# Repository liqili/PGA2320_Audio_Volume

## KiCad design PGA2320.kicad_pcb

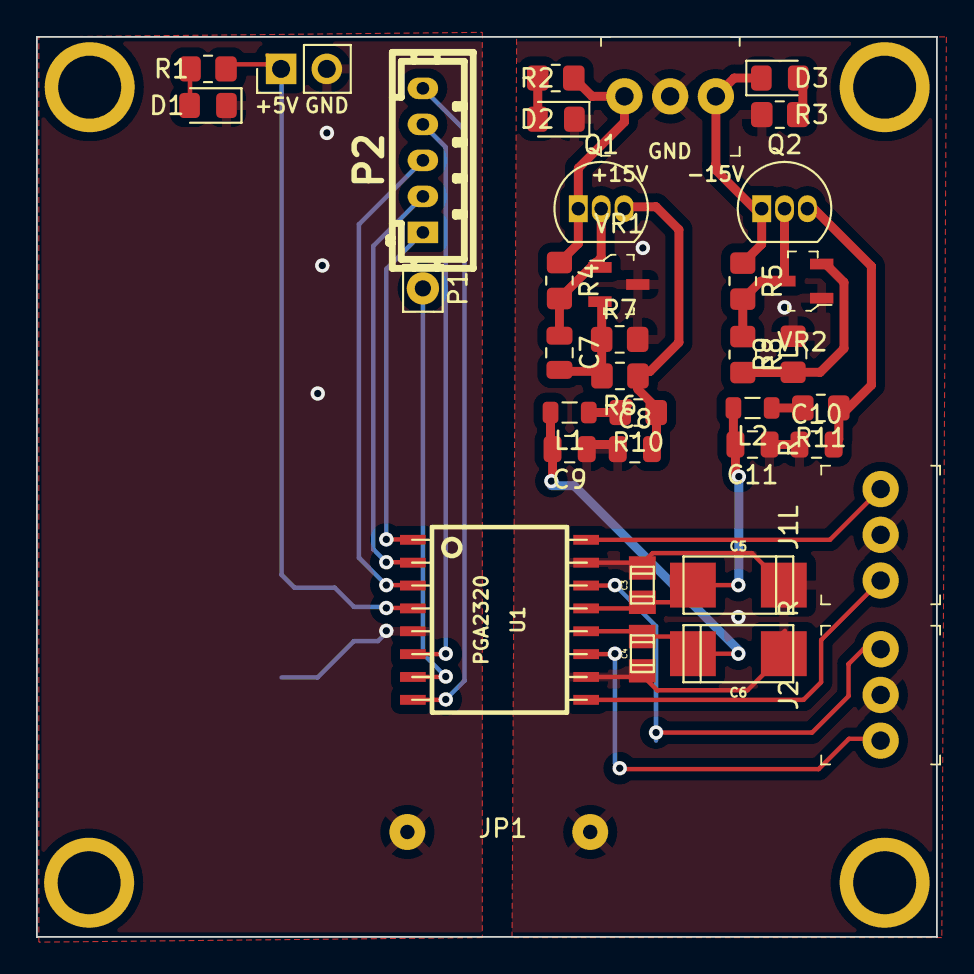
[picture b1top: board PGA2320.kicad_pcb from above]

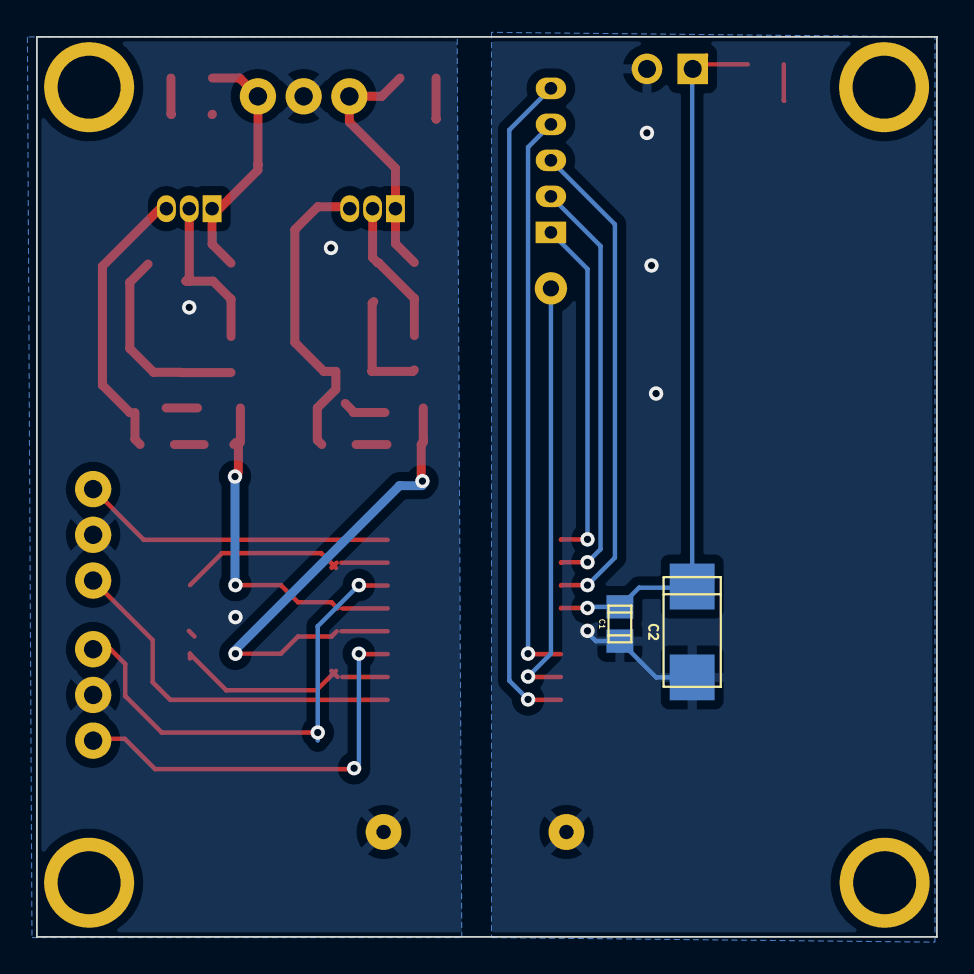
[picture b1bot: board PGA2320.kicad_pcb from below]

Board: 2 copper layers, 50.0 x 50.0 mm, 39 parts (2 on the bottom side), 28 nets.

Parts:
C1: 0.1uf; c_0805
C2: 10uf; c_tant_C
C3, C4: 0.1uF; c_0805
C5, C6: 10uF; c_tant_C
C7: 100pf; C_0805_2012Metric
C8, C9, C10, C11: 10uf; C_0805_2012Metric
D1, D2, D3: LED; LED_0805_2012Metric_Pad1.15x1.40mm_HandSolder
J1, J2: XH2.54-3P; PinHeader_1x3_P2.54mm_Drill1.02mm
J3: 2P-2.54; PinHeader_1x02_P2.54mm_Vertical
J4: 3P-2.54; PinHeader_1x3_P2.54mm_Drill1.02mm
JP1: JUMPER; WireConnection_0-8mmDrill
L1, L2: 47uH; L_0805_2012Metric
P1: SDO_TO_OTHER_PGA2311; Pin_D0.9mm_L10.0mm_W2.4mm_FlatFork
P2: CONTROLLER; b5b-ph-kl
Q1: BC550; TO-92_Inline
Q2: BC560; TO-92_Inline
R1, R2, R3: 10k; R_0805_2012Metric_Pad1.20x1.40mm_HandSolder
R4, R5: 1k; R_0805_2012Metric_Pad1.20x1.40mm_HandSolder
R6: 25k; R_0805_2012Metric_Pad1.20x1.40mm_HandSolder
R7, R8: 5k; R_0805_2012Metric_Pad1.20x1.40mm_HandSolder
R9: 26.2k; R_0805_2012Metric_Pad1.20x1.40mm_HandSolder
R10, R11: 10; R_0805_2012Metric_Pad1.20x1.40mm_HandSolder
U1: PGA2320; soic-16-PGA2320
VR1, VR2: TL431AIDBZR; SOT-23-3

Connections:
+5VD: C1.1, C2.1, J3.1, R1.2, U1.4 (VD+)
+15V: C4.1, C6.1, C9.2, L1.2, U1.12 (VA+)
-15V: C3.2, C5.2, C11.2, L2.2, U1.13 (VA-)
/+16V to +18V: J4.1, Q1.1 (C), R2.1, R4.1
/-16V to -18V: D3.1 (K), J4.3, Q2.1 (C), R5.1
CS: P2.2, U1.2 (*CS)
GND_A: C3.1, C4.2, C5.1, C6.2, C8.1, C9.1, C10.1, C11.1, D2.1 (K), J1.2, J2.2, J4.2, JP1.1 (A), R3.1, R7.2, R9.2, U1.10 (AGNDR), U1.15 (AGNDL), VR1.3 (A), VR2.1 (K)
GND_D: C1.2, C2.2, D1.1 (K), J3.2, JP1.2 (B), U1.5 (DGND)
MUTE: P2.5, U1.8 (*MUTE)
unnamed: D1.2 (A), R1.1
unnamed: D2.2 (A), R2.2
unnamed: D3.2 (A), R3.2
unnamed: L1.1, R10.2
unnamed: L2.1, R11.2
unnamed: C7.1, Q1.2 (B), R4.2, VR1.1 (K)
unnamed: C8.2, Q1.3 (E), R6.1, R10.1
unnamed: Q2.2 (B), R5.2, R8.1, VR2.3 (A)
unnamed: C10.2, Q2.3 (E), R11.1
unnamed: C7.2, R6.2, R7.1, VR1.2 (REF)
unnamed: R8.2, R9.1, VR2.2 (REF)
SCLK: P2.4, U1.6 (SCLK)
SDI: P2.3, U1.3 (SDI)
SDO: P1.1, U1.7 (SDO)
VIN_L: J1.1, U1.16 (VINL)
VIN_R: J1.3, U1.9 (VINR)
VOUT_L: J2.1, U1.14 (VOUTL)
VOUT_R: J2.3, U1.11 (VOUTR)
ZCEN: P2.1, U1.1 (ZCEN)

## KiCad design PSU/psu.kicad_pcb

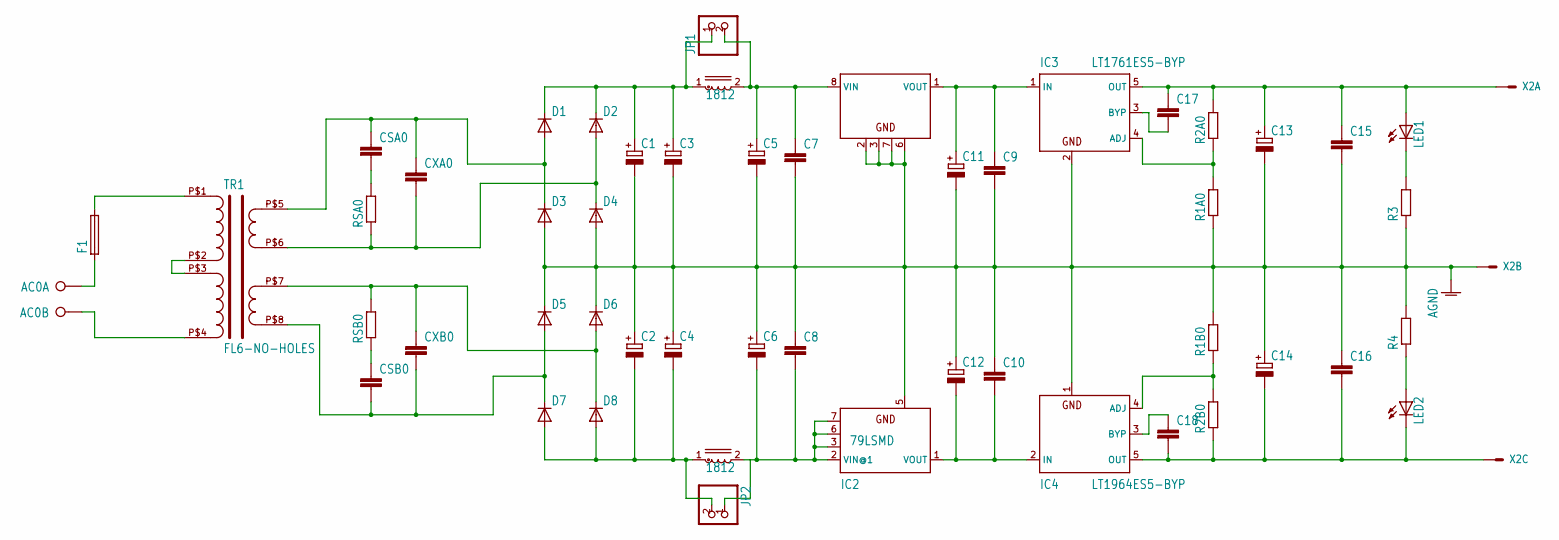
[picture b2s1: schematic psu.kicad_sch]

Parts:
AC0: W237-02P; W237-132
C1, C2, C3, C4, C5, C6: CPOL-EUE5-10.5; E5-10,5
C7, C8, C9, C10, C17, C18: C-EUC1206; C1206
C11, C12, C13, C14: CPOL-EUD; PANASONIC_D
C15, C16: C-EUC4532; C4532
CSA0: C-EUC1210; C1210
CSB0: C-EUC1210; C1210
CXA0: C-EUC1210; C1210
CXB0: C-EUC1210; C1210
D1, D2, D3, D4, D5, D6, D7, D8: DIODE-DO214AC; DO214AC
F1: GSH15
IC1: 78LSMD; SOIC08
IC2: 79LSMD; SOIC08
IC3: LT1761ES5-BYP; SOT23-5
IC4: LT1964ES5-BYP; SOT23-5
JP1, JP2: PINHD-1X2; 1X02
L1, L2: 1812
LED1, LED2: LEDCHIPLED_0805; CHIPLED_0805
R1A0, R1B0, R2A0, R2B0: R-EU_R0805; R0805
R3, R4: R-EU_R1206; R1206
RSA0: R-EU_R1206; R1206
RSB0: R-EU_R1206; R1206
TR1: FL6-NO-HOLES
X2: 22-23-2031

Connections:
AGND: C1.-, C2.+, C3.-, C4.+, C5.-, C6.+, C7.2, C8.1, C9.2, C10.1, C11.-, C12.+, C13.-, C14.+, C15.2, C16.1, D3.A, D4.A, D5.C, D6.C, IC1.2 (GND@1), IC1.3 (GND@2), IC1.6 (GND@4), IC1.7 (GND@3), IC2.5 (GND), IC3.2 (GND), IC4.1 (GND), R1A0.1, R1B0.2, R3.1, R4.2, X2.2
C14: C14.-, C16.2, C18.2, IC4.5 (OUT), LED2.C, R2B0.1, X2.3
unnamed: TR1.P$2 (PRI1B), TR1.P$3 (PRI2A)
unnamed: F1.2, TR1.P$1 (PRI1A)
unnamed: AC0.2, TR1.P$4 (PRI2B)
unnamed: AC0.1, F1.1
unnamed: CSA0.2, RSA0.2
unnamed: LED2.A, R4.1
unnamed: C17.2, IC3.3 (BYP)
unnamed: LED1.C, R3.2
unnamed: C9.1, C11.+, IC1.1 (VOUT), IC3.1 (IN)
unnamed: C13.+, C15.1, C17.1, IC3.5 (OUT), LED1.A, R2A0.2, X2.1
unnamed: IC4.4 (ADJ), R1B0.1, R2B0.2
unnamed: IC3.4 (ADJ), R1A0.2, R2A0.1
unnamed: CXA0.2, D2.A, D4.C, RSA0.1, TR1.P$6 (SEC1B)
unnamed: CSA0.1, CXA0.1, D1.A, D3.C, TR1.P$5 (SEC1A)
unnamed: CSB0.2, CXB0.2, D5.A, D7.C, TR1.P$8 (SEC2B)
unnamed: C10.2, C12.-, IC2.1 (VOUT), IC4.2 (IN)
unnamed: C18.1, IC4.3 (BYP)
unnamed: C5.+, C7.1, IC1.8 (VIN), JP1.2, L1.2
unnamed: C2.-, C4.-, D7.A, D8.A, JP2.2, L2.1
unnamed: C6.-, C8.2, IC2.2 (VIN@1), IC2.3 (VIN@2), IC2.6 (VIN@3), IC2.7 (VIN@4), JP2.1, L2.2
unnamed: CXB0.1, D6.A, D8.C, RSB0.2, TR1.P$7 (SEC2A)
unnamed: CSB0.1, RSB0.1
unnamed: C1.+, C3.+, D1.C, D2.C, JP1.1, L1.1

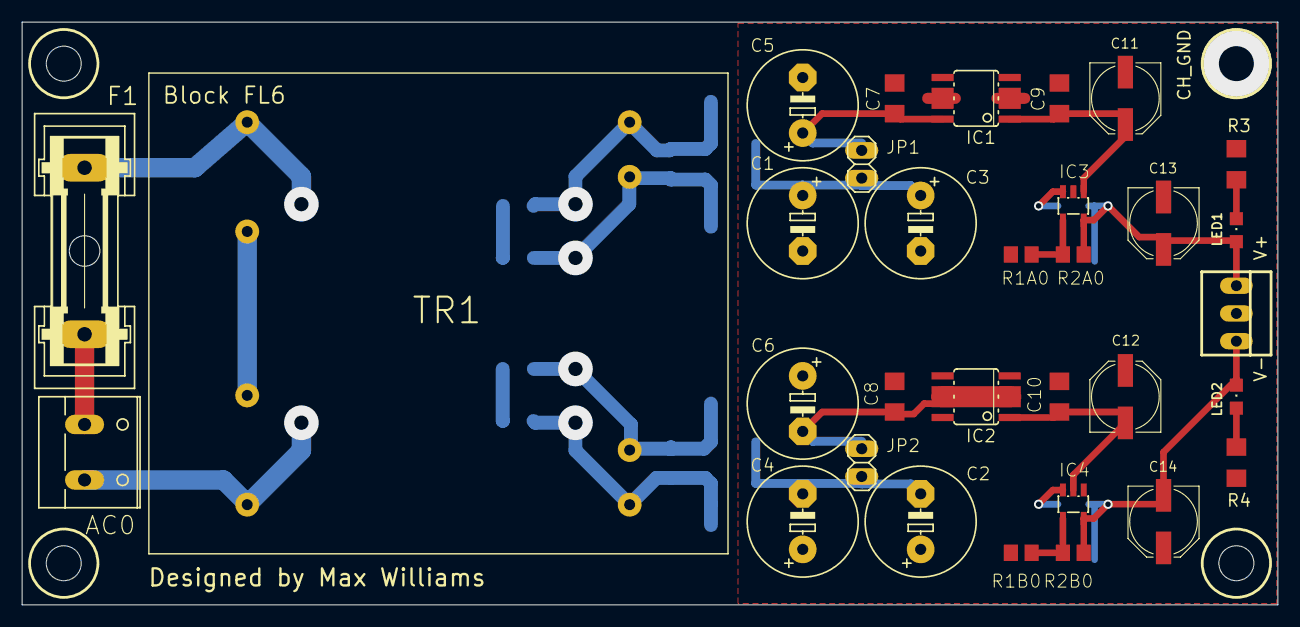
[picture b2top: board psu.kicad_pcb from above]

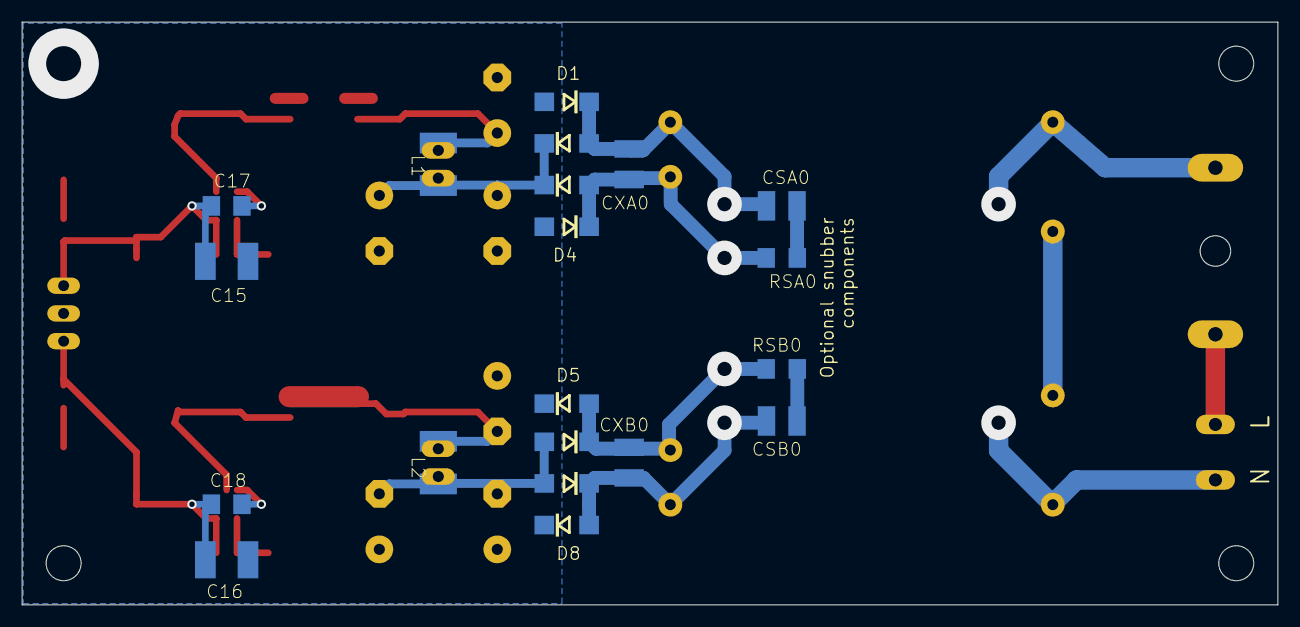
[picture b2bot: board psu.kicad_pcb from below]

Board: 2 copper layers, 114.9 x 53.3 mm, 55 parts (20 on the bottom side), 25 nets.

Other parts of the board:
@HOLE0, @HOLE1, @HOLE2: (no value)

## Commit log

2024-06-29 inital
2024-06-29 add libs
2024-07-02 pcb layout
2024-07-02 remove tmp files
2024-07-03 layout
2024-07-04 finish first version
2024-07-04 improve silk screen
2024-07-04 improvements
2024-07-06 add psu module
2024-07-06 move PSU away
2024-07-07 add regulator circuit
2024-07-07 psu payout
2024-07-08 add PI filter
2024-07-12 add power supply for vdd
2025-03-29 scheme
